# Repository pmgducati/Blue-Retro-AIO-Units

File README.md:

# Blue Retro AIO PCBs
This is a collection of PCBs that I made to work with darthcloud's BlueRetro Project. (https://github.com/darthcloud/BlueRetro)  The PCB's were created in Eagle and I have included the Gerbers if you would like to build them yourself. 

I have created PCB's for all supported systems with the exception of JVS.  An issue has been created for each of the systems that need testing.  If you make one please comment in the related issue on any progress/issues.

Currently, I am working on the Virtual Boy PCB, but need to find a cost efficient controller plug (I am not consolizing mine).  

Amaiorano wrote up a review for the variants that they built, you can read it here:
https://amaiorano.io/2023/11/06/blueretro-aio.html

Current status of all systems:

Here are some pics of the PCBs and Housings:

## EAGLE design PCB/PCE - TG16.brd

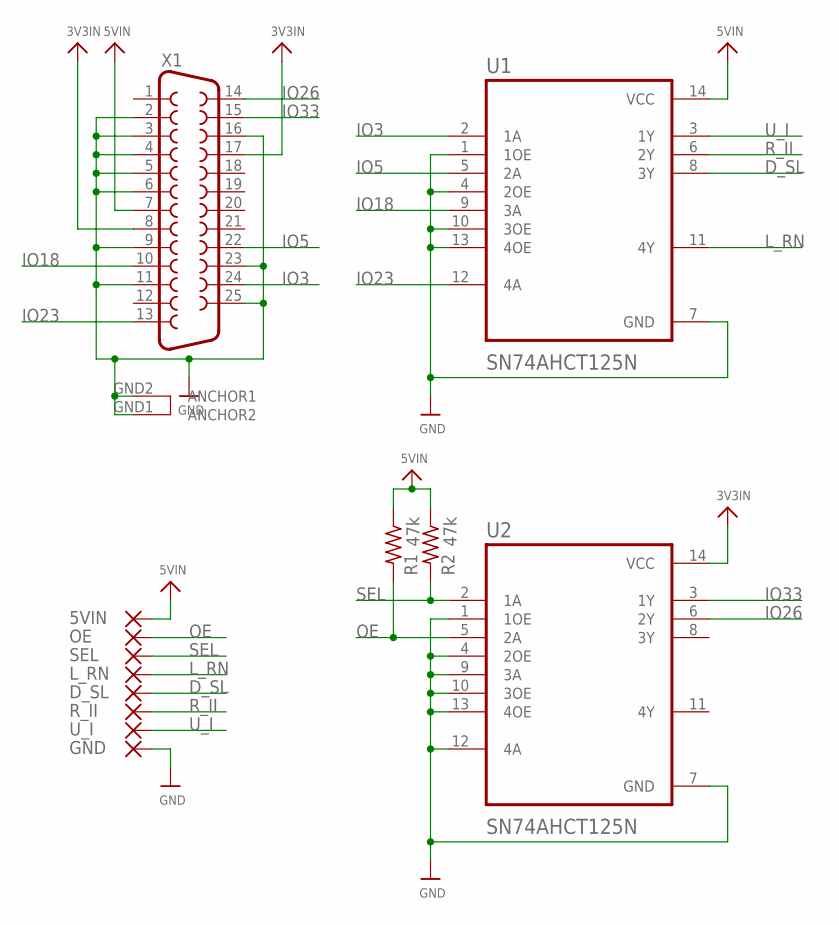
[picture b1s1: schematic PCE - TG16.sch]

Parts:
5VIN: SMD5; SMD2,54-5,08
D_SL: SMD5; SMD2,54-5,08
GND: SMD5; SMD2,54-5,08
L_RN: SMD5; SMD2,54-5,08
OE: SMD5; SMD2,54-5,08
R1, R2: 47k; R1206
R_II: SMD5; SMD2,54-5,08
SEL: SMD5; SMD2,54-5,08
U1, U2: SN74AHCT125N; DIP794W45P254L1969H508Q14
U_I: SMD5; SMD2,54-5,08
X1: DB25_FEMALEHP; F25HP

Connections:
3V3IN: U2.14 (VCC), X1.8, X1.17
5VIN: 5VIN.1, R1.1, R2.1, U1.14 (VCC), X1.7
D_SL: D_SL.1, U1.8 (3Y)
GND: GND.1, U1.1 (1OE), U1.4 (2OE), U1.7 (GND), U1.10 (3OE), U1.13 (4OE), U2.1 (1OE), U2.4 (2OE), U2.7 (GND), U2.9 (3A), U2.10 (3OE), U2.12 (4A), U2.13 (4OE), X1.2, X1.3, X1.4, X1.5, X1.6, X1.9, X1.11, X1.16, X1.23, X1.25, X1.GND1 (ANCHOR2), X1.GND2 (ANCHOR1)
IO3: U1.2 (1A), X1.24
IO5: U1.5 (2A), X1.22
IO18: U1.9 (3A), X1.10
IO23: U1.12 (4A), X1.13
IO26: U2.6 (2Y), X1.14
IO33: U2.3 (1Y), X1.15
L_RN: L_RN.1, U1.11 (4Y)
OE: OE.1, R1.2, U2.5 (2A)
R_II: R_II.1, U1.6 (2Y)
SEL: R2.2, SEL.1, U2.2 (1A)
U_I: U1.3 (1Y), U_I.1

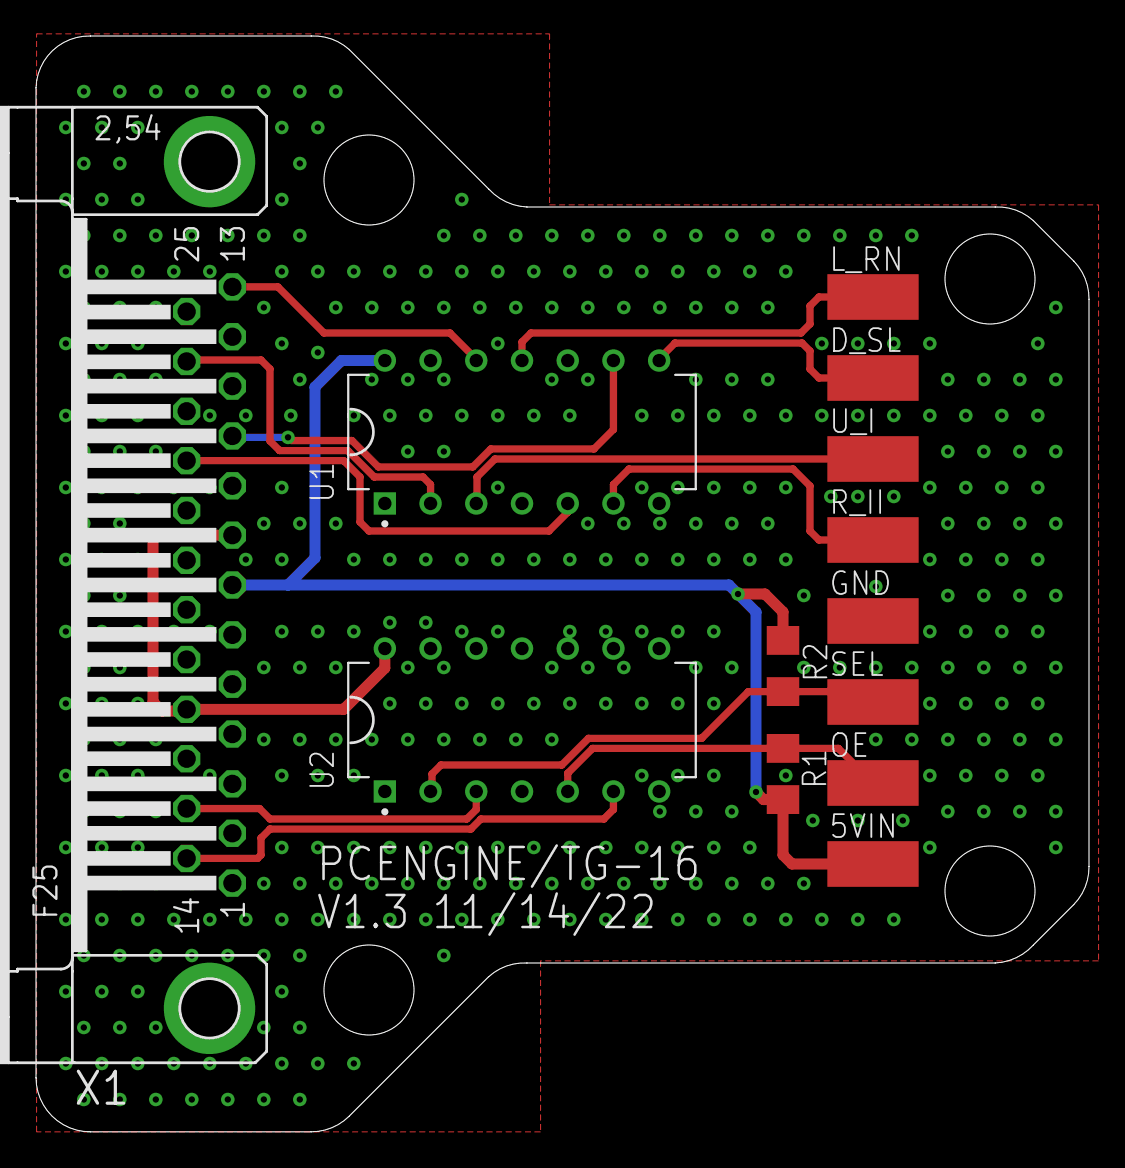
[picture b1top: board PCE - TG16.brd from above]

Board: 2 copper layers, 58.5 x 60.9 mm, 13 parts (0 on the bottom side), 15 nets.

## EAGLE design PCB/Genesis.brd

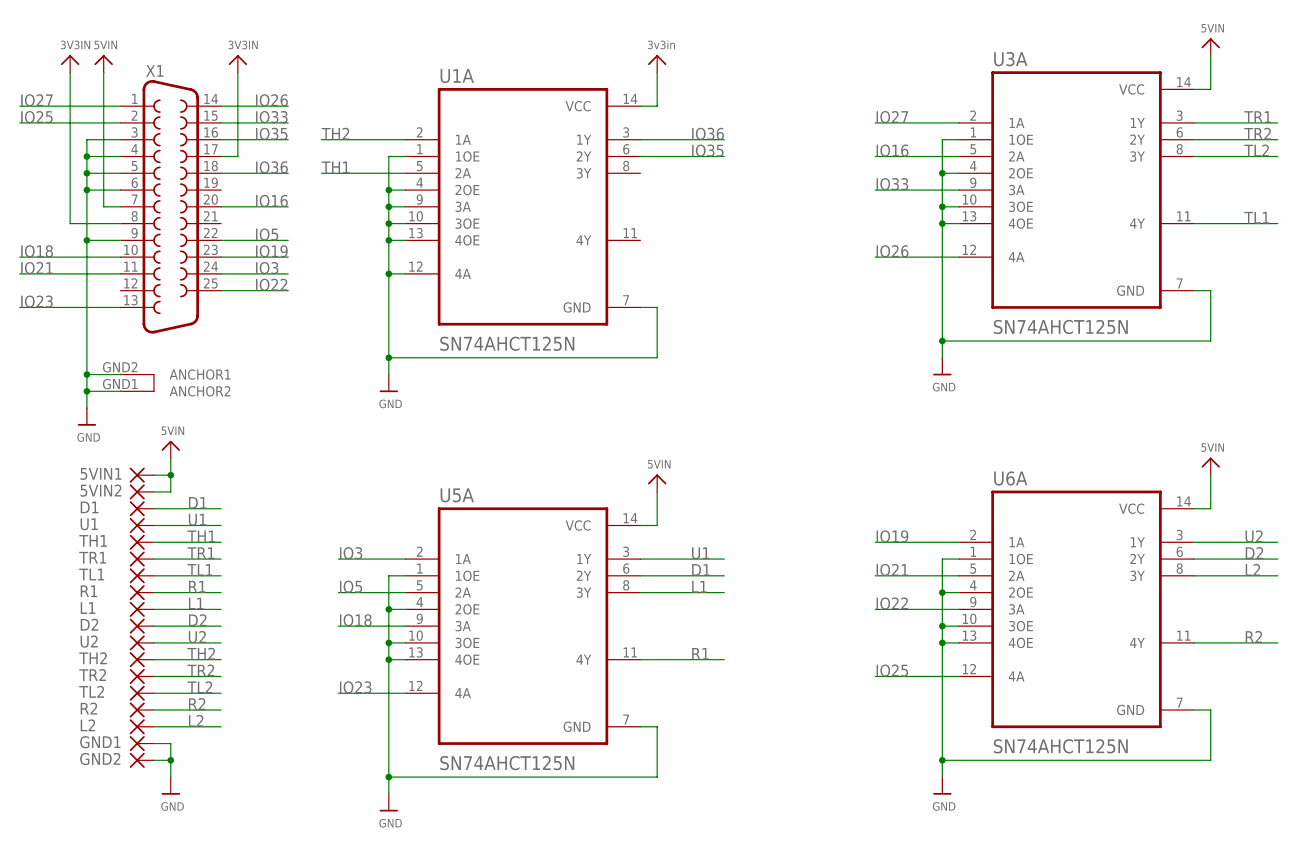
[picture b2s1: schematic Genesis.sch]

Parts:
5VIN1, 5VIN2: SMD5; SMD2,54-5,08
D1, D2: SMD5; SMD2,54-5,08
GND1, GND2: SMD5; SMD2,54-5,08
L1, L2: SMD5; SMD2,54-5,08
R1, R2: SMD5; SMD2,54-5,08
TH1, TH2: SMD5; SMD2,54-5,08
TL1, TL2: SMD5; SMD2,54-5,08
TR1, TR2: SMD5; SMD2,54-5,08
U1, U2: SMD5; SMD2,54-5,08
U1A, U3A, U5A, U6A: SN74AHCT125N; DIP794W45P254L1969H508Q14
X1: DB25_FEMALEHP; F25HP

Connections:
3V3IN: U1A.14 (VCC), X1.8, X1.17
5VIN: 5VIN1.1, 5VIN2.1, U3A.14 (VCC), U5A.14 (VCC), U6A.14 (VCC), X1.7
D1: D1.1, U5A.6 (2Y)
D2: D2.1, U6A.6 (2Y)
GND: GND1.1, GND2.1, U1A.1 (1OE), U1A.4 (2OE), U1A.7 (GND), U1A.9 (3A), U1A.10 (3OE), U1A.12 (4A), U1A.13 (4OE), U3A.1 (1OE), U3A.4 (2OE), U3A.7 (GND), U3A.10 (3OE), U3A.13 (4OE), U5A.1 (1OE), U5A.4 (2OE), U5A.7 (GND), U5A.10 (3OE), U5A.13 (4OE), U6A.1 (1OE), U6A.4 (2OE), U6A.7 (GND), U6A.10 (3OE), U6A.13 (4OE), X1.3, X1.4, X1.5, X1.6, X1.9, X1.GND1 (ANCHOR2), X1.GND2 (ANCHOR1)
IO3: U5A.2 (1A), X1.24
IO5: U5A.5 (2A), X1.22
IO16: U3A.5 (2A), X1.20
IO18: U5A.9 (3A), X1.10
IO19: U6A.2 (1A), X1.23
IO21: U6A.5 (2A), X1.11
IO22: U6A.9 (3A), X1.25
IO23: U5A.12 (4A), X1.13
IO25: U6A.12 (4A), X1.2
IO26: U3A.12 (4A), X1.14
IO27: U3A.2 (1A), X1.1
IO33: U3A.9 (3A), X1.15
IO35: U1A.6 (2Y), X1.16
IO36: U1A.3 (1Y), X1.18
L1: L1.1, U5A.8 (3Y)
L2: L2.1, U6A.8 (3Y)
R1: R1.1, U5A.11 (4Y)
R2: R2.1, U6A.11 (4Y)
TH1: TH1.1, U1A.5 (2A)
TH2: TH2.1, U1A.2 (1A)
TL1: TL1.1, U3A.11 (4Y)
TL2: TL2.1, U3A.8 (3Y)
TR1: TR1.1, U3A.3 (1Y)
TR2: TR2.1, U3A.6 (2Y)
U1: U1.1, U5A.3 (1Y)
U2: U2.1, U6A.3 (1Y)

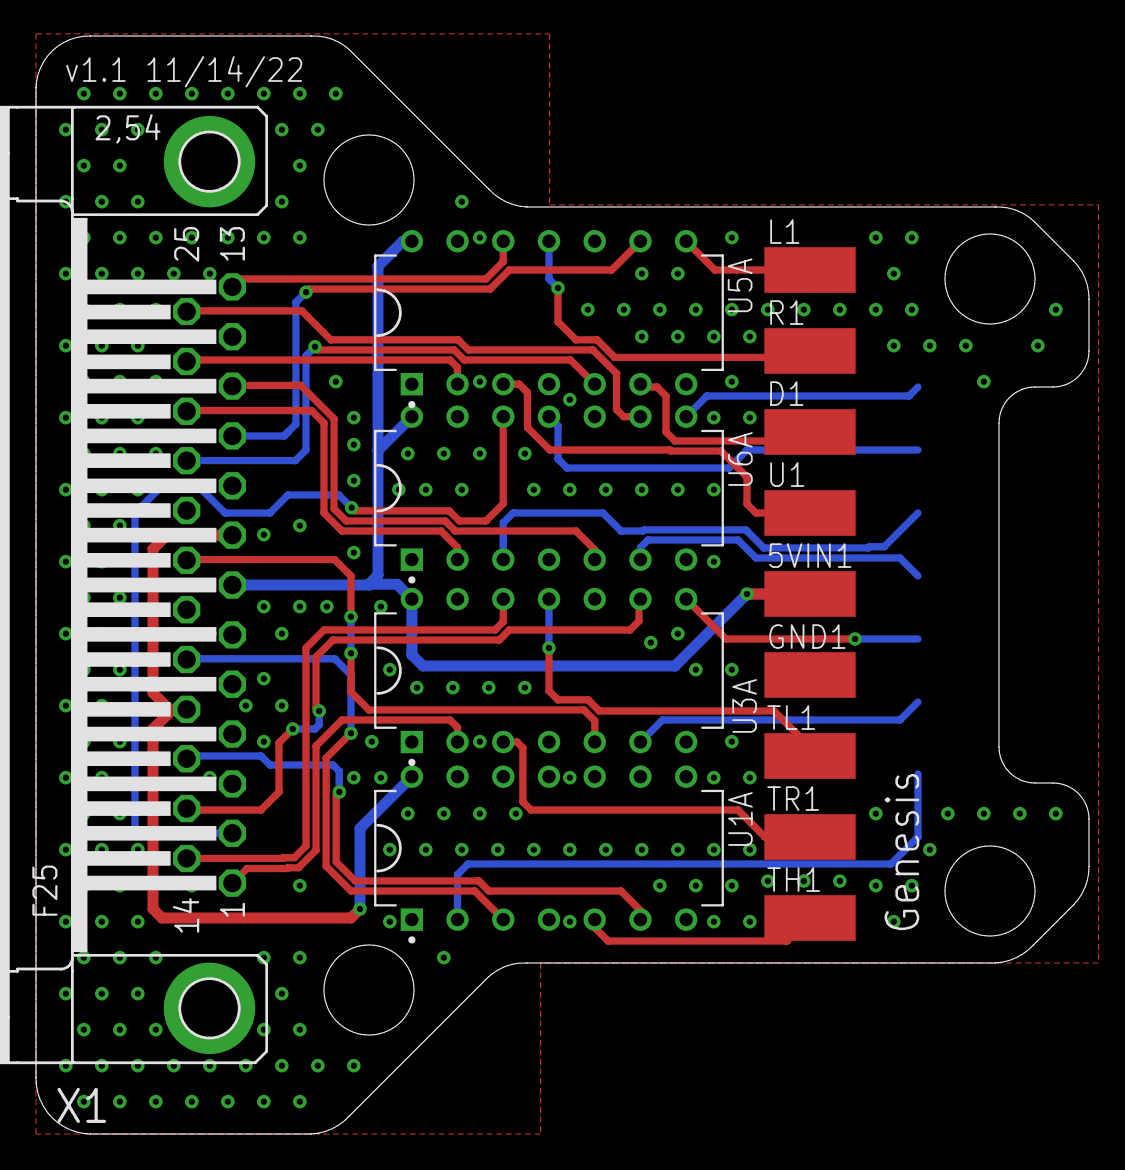
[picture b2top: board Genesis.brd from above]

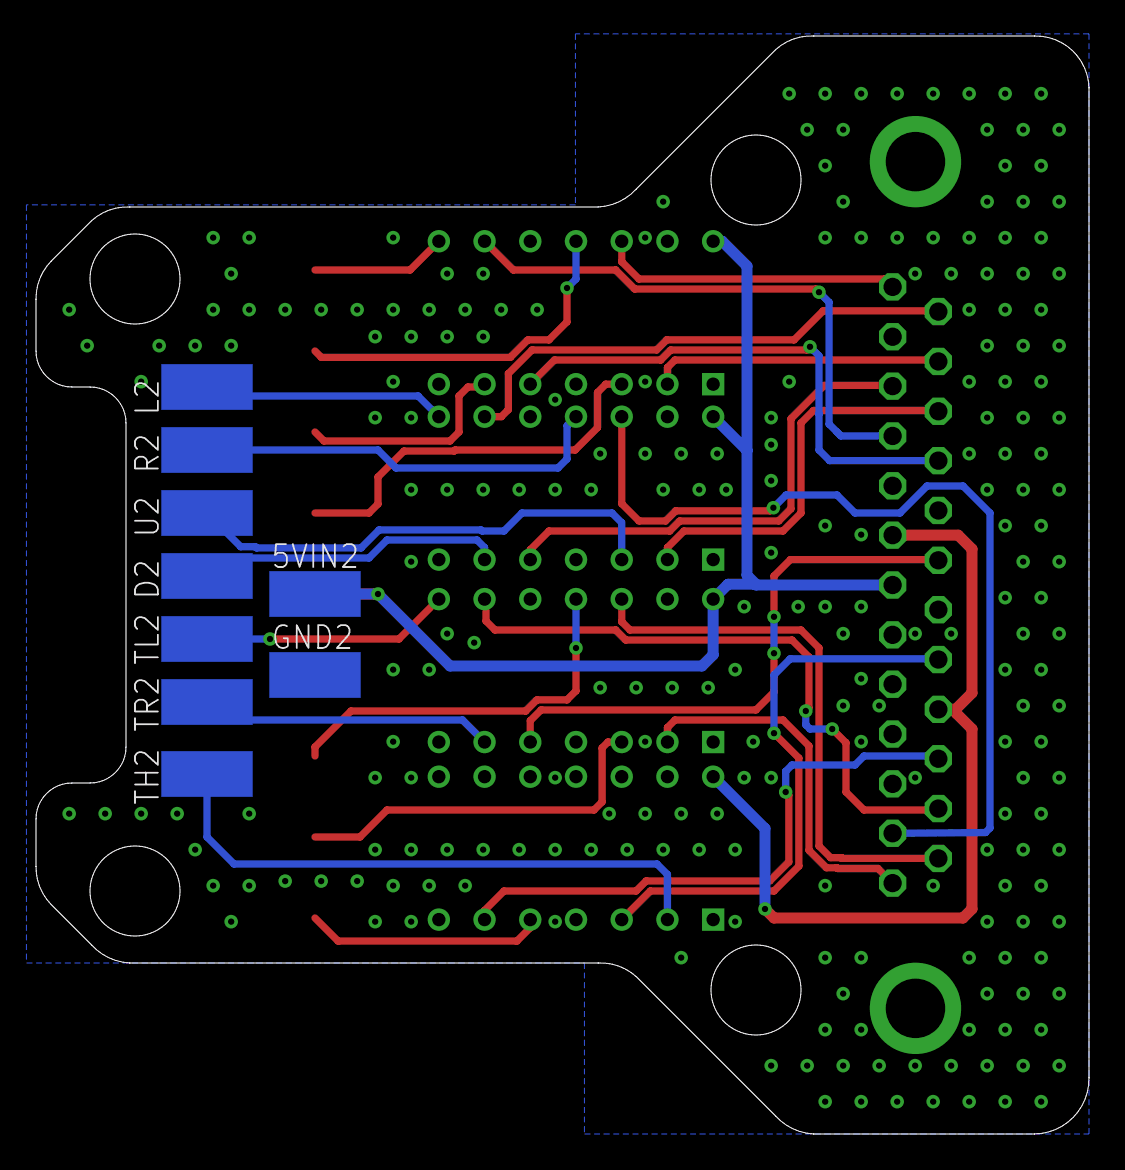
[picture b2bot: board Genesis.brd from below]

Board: 2 copper layers, 58.5 x 61.0 mm, 23 parts (9 on the bottom side), 31 nets.

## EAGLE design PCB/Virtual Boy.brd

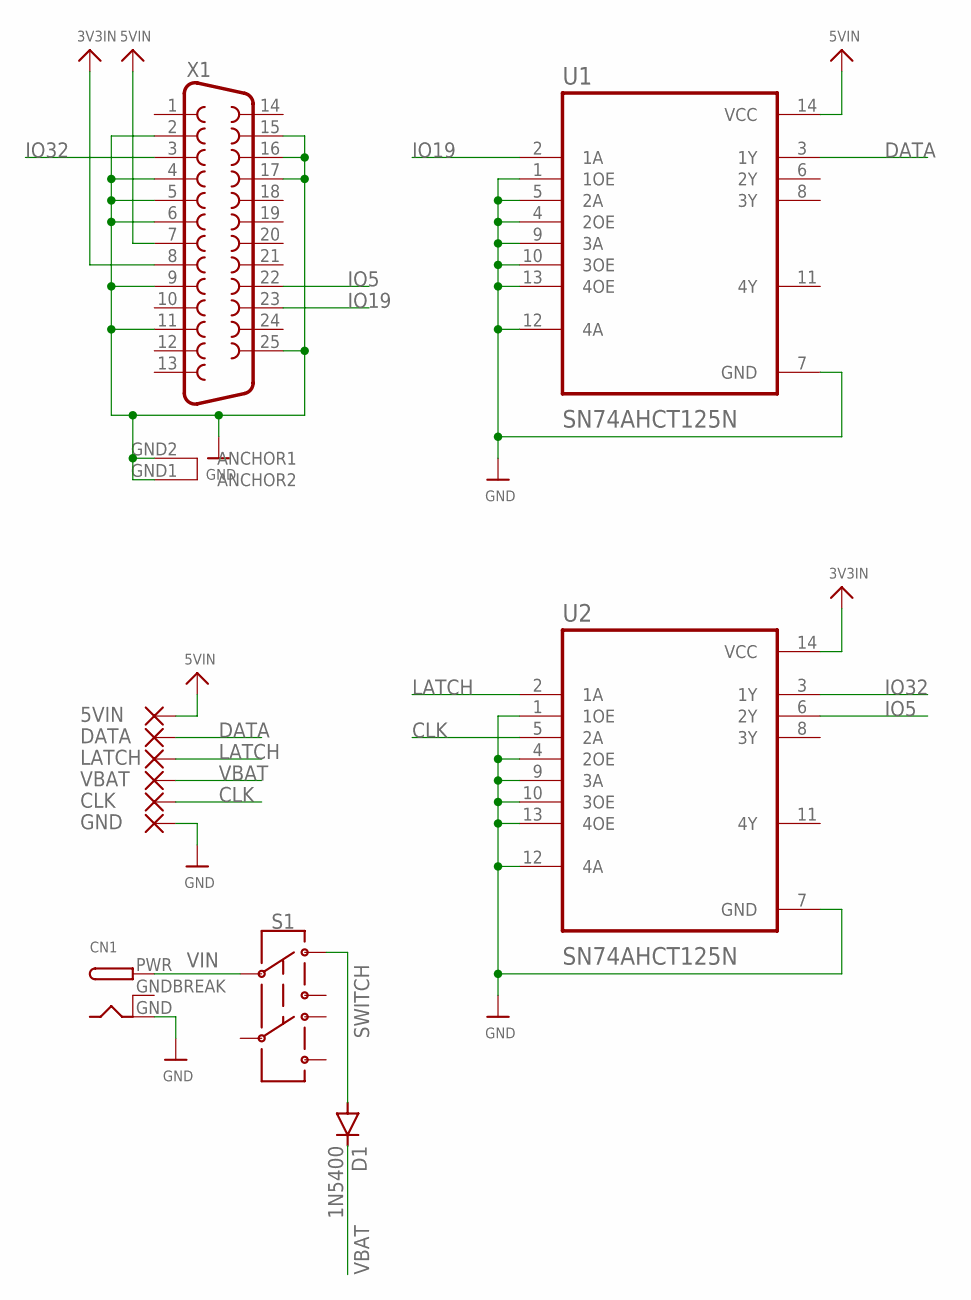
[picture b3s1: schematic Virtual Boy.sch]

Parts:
5VIN: SMD5; SMD2,54-5,08
CLK: SMD5; SMD2,54-5,08
CN1: DCBARRELPTH; DCJACK_2MM_PTH
D1: 1N5400; DO201-15
DATA: SMD5; SMD2,54-5,08
GND: SMD5; SMD2,54-5,08
LATCH: SMD5; SMD2,54-5,08
S1: SWITCH-DPDT-PTH-GPI-152-3013; SWITCH_DPDT_PTH_GPI-152-3013
U1, U2: SN74AHCT125N; DIP794W45P254L1969H508Q14
VBAT: SMD5; SMD2,54-5,08
X1: DB25_FEMALEHP; F25HP

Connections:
3V3IN: U2.14 (VCC), X1.8
5VIN: 5VIN.1, U1.14 (VCC), X1.7
CLK: CLK.1, U2.5 (2A)
DATA: DATA.1, U1.3 (1Y)
GND: CN1.GND, GND.1, U1.1 (1OE), U1.4 (2OE), U1.5 (2A), U1.7 (GND), U1.9 (3A), U1.10 (3OE), U1.12 (4A), U1.13 (4OE), U2.1 (1OE), U2.4 (2OE), U2.7 (GND), U2.9 (3A), U2.10 (3OE), U2.12 (4A), U2.13 (4OE), X1.2, X1.4, X1.5, X1.6, X1.9, X1.11, X1.15, X1.16, X1.17, X1.25, X1.GND1 (ANCHOR2), X1.GND2 (ANCHOR1)
GNDBREAK: CN1.GNDBREAK
IO5: U2.6 (2Y), X1.22
IO19: U1.2 (1A), X1.23
IO32: U2.3 (1Y), X1.3
LATCH: LATCH.1, U2.2 (1A)
SWITCH: D1.A, S1.10 (1)
VBAT: D1.C, VBAT.1
VIN: CN1.PWR, S1.C@1 (2)

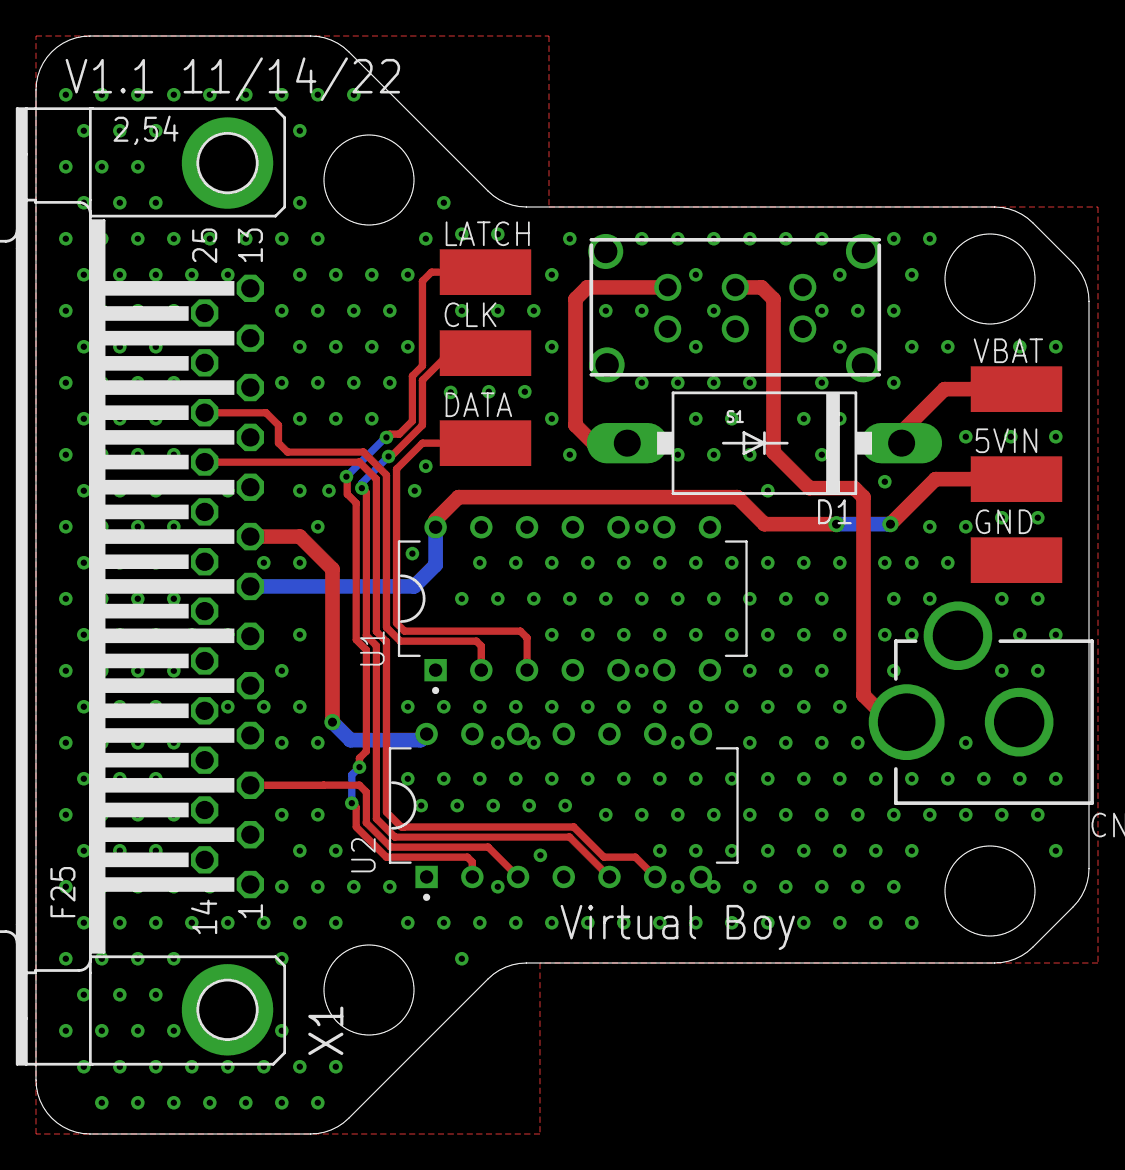
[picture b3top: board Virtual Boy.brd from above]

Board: 2 copper layers, 58.5 x 61.0 mm, 12 parts (0 on the bottom side), 12 nets.

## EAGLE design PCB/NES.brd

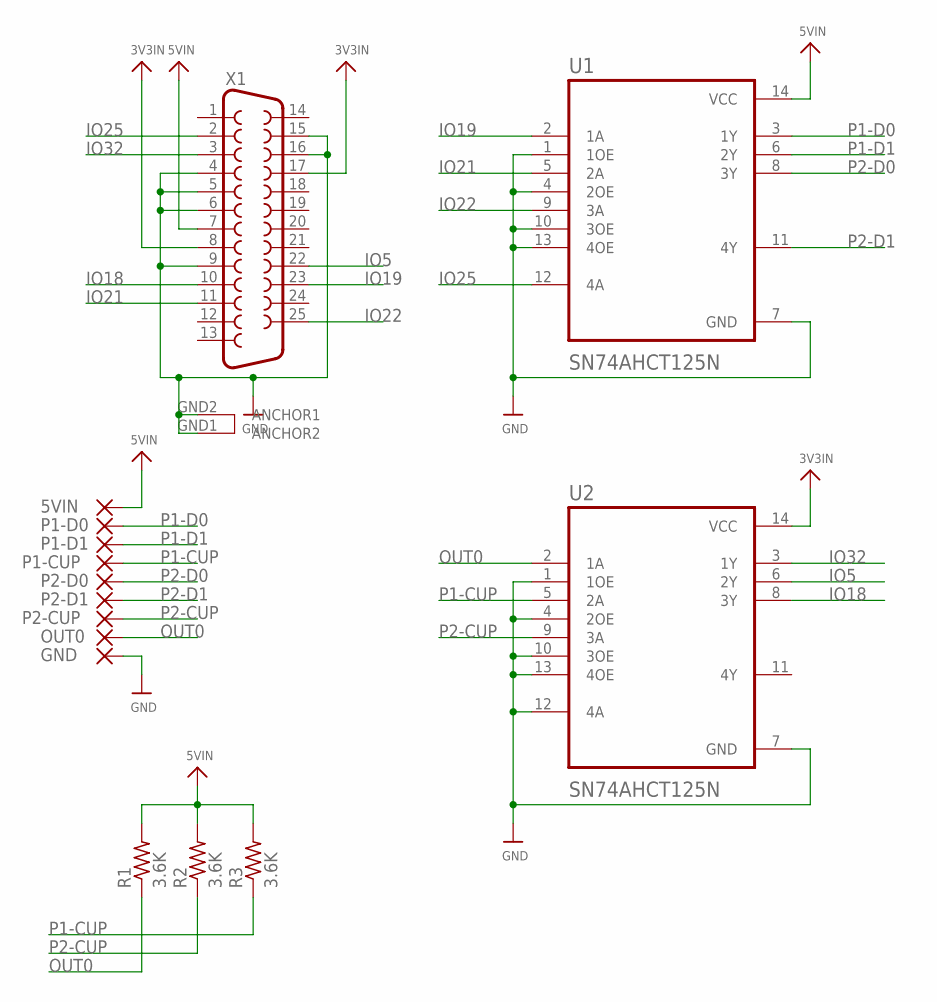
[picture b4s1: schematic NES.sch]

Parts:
5VIN: SMD5; SMD2,54-5,08
GND: SMD5; SMD2,54-5,08
OUT0: SMD5; SMD2,54-5,08
P1-CUP, P1-D0, P1-D1, P2-CUP, P2-D0, P2-D1: SMD5; SMD2,54-5,08
R1, R2, R3: 3.6K; R1206
U1, U2: SN74AHCT125N; DIP794W45P254L1969H508Q14
X1: DB25_FEMALEHP; F25HP

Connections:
3V3IN: U2.14 (VCC), X1.8, X1.17
5VIN: 5VIN.1, R1.2, R2.2, R3.2, U1.14 (VCC), X1.7
GND: GND.1, U1.1 (1OE), U1.4 (2OE), U1.7 (GND), U1.10 (3OE), U1.13 (4OE), U2.1 (1OE), U2.4 (2OE), U2.7 (GND), U2.10 (3OE), U2.12 (4A), U2.13 (4OE), X1.4, X1.5, X1.6, X1.9, X1.15, X1.16, X1.GND1 (ANCHOR2), X1.GND2 (ANCHOR1)
IO5: U2.6 (2Y), X1.22
IO18: U2.8 (3Y), X1.10
IO19: U1.2 (1A), X1.23
IO21: U1.5 (2A), X1.11
IO22: U1.9 (3A), X1.25
IO25: U1.12 (4A), X1.2
IO32: U2.3 (1Y), X1.3
OUT0: OUT0.1, R1.1, U2.2 (1A)
P1-CUP: P1-CUP.1, R3.1, U2.5 (2A)
P1-D0: P1-D0.1, U1.3 (1Y)
P1-D1: P1-D1.1, U1.6 (2Y)
P2-CUP: P2-CUP.1, R2.1, U2.9 (3A)
P2-D0: P2-D0.1, U1.8 (3Y)
P2-D1: P2-D1.1, U1.11 (4Y)

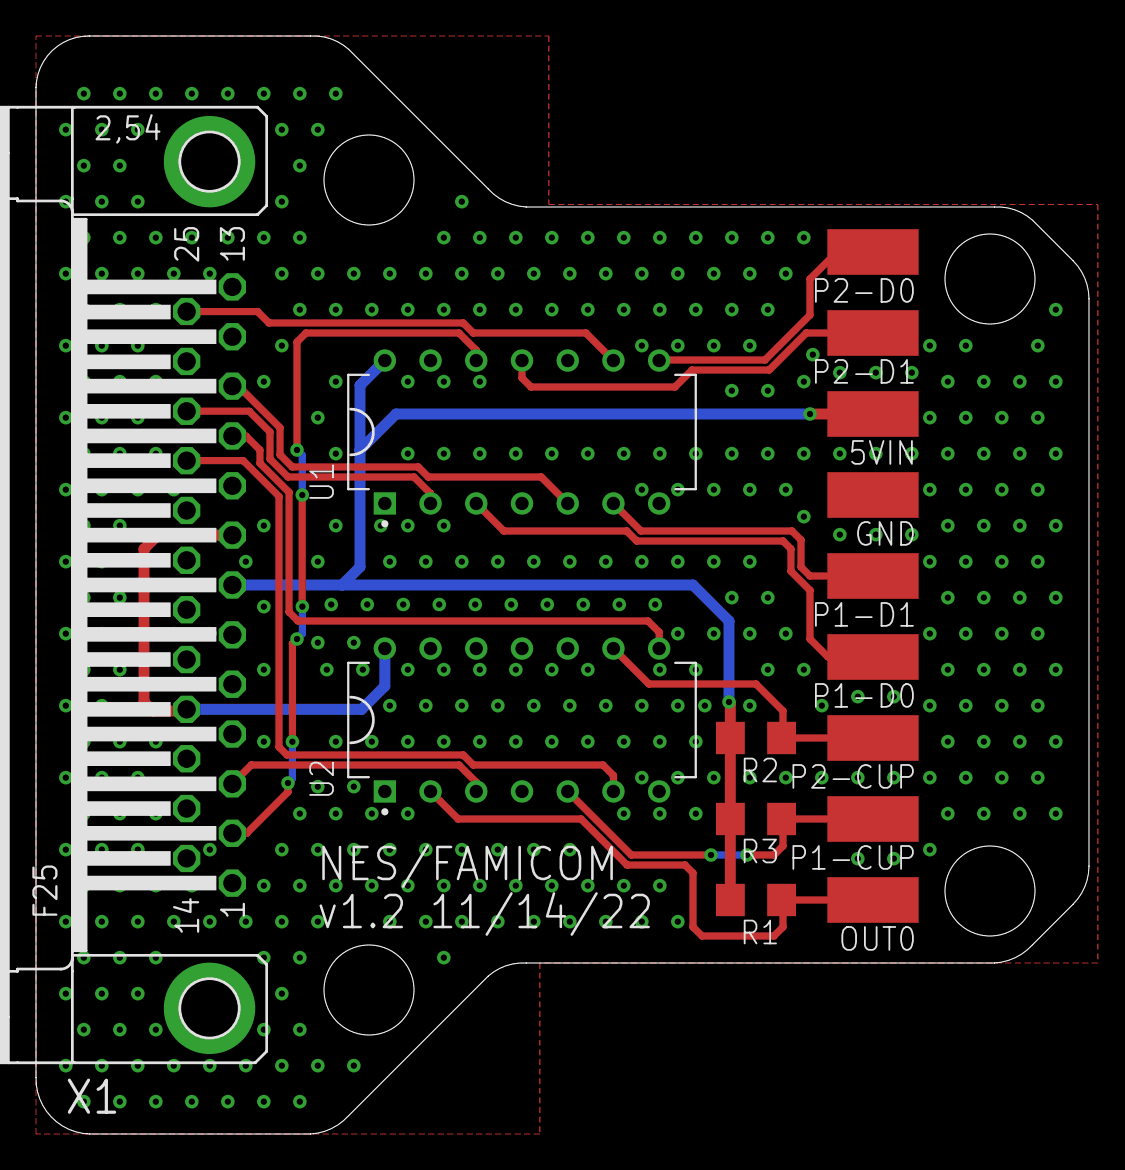
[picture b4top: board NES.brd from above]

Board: 2 copper layers, 58.5 x 61.0 mm, 15 parts (0 on the bottom side), 17 nets.

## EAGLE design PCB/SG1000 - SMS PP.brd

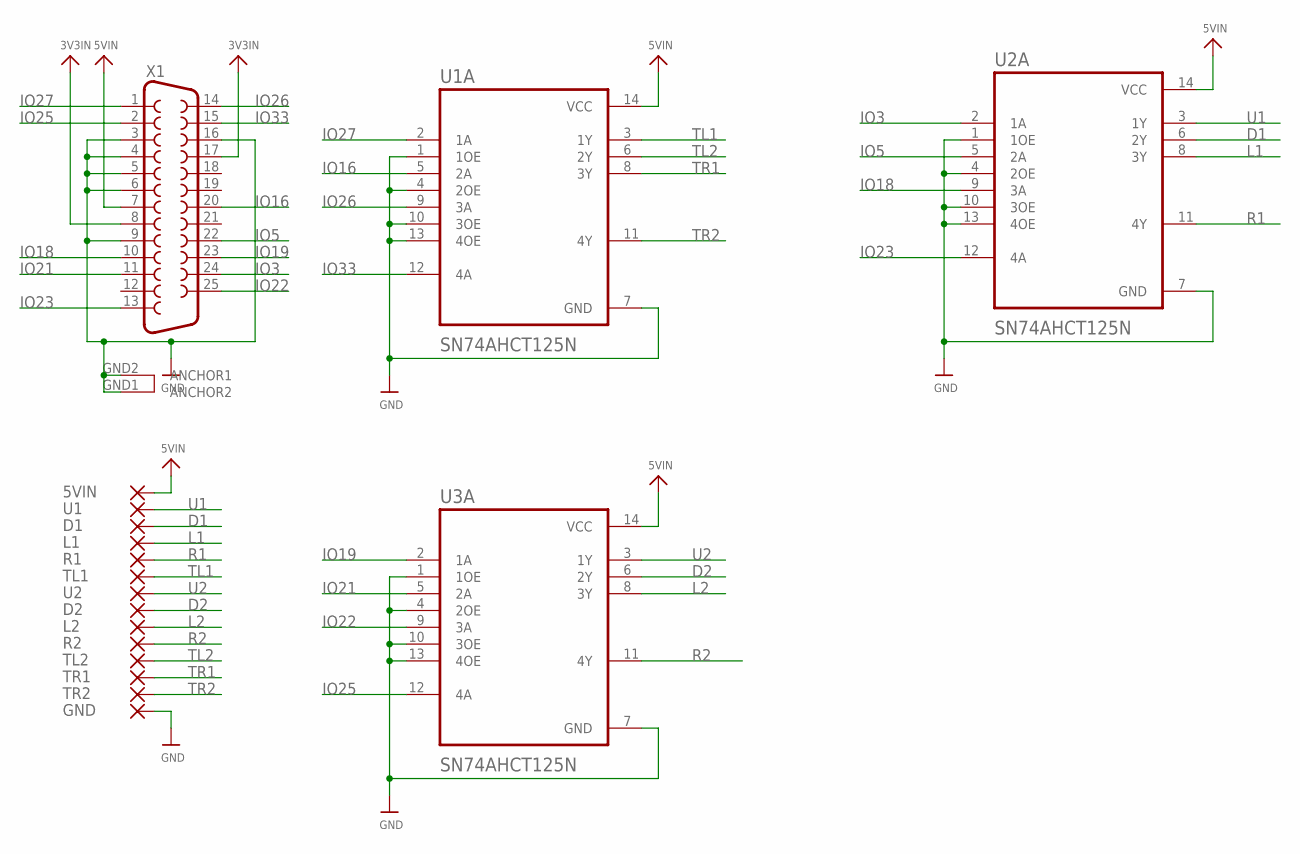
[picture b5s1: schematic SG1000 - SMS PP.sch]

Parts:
5VIN: SMD5; SMD2,54-5,08
D1, D2: SMD5; SMD2,54-5,08
GND: SMD5; SMD2,54-5,08
L1, L2: SMD5; SMD2,54-5,08
R1, R2: SMD5; SMD2,54-5,08
TL1, TL2: SMD5; SMD2,54-5,08
TR1, TR2: SMD5; SMD2,54-5,08
U1, U2: SMD5; SMD2,54-5,08
U1A, U2A, U3A: SN74AHCT125N; DIP794W45P254L1969H508Q14
X1: DB25_FEMALEHP; F25HP

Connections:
3V3IN: X1.8, X1.17
5VIN: 5VIN.1, U1A.14 (VCC), U2A.14 (VCC), U3A.14 (VCC), X1.7
D1: D1.1, U2A.6 (2Y)
D2: D2.1, U3A.6 (2Y)
GND: GND.1, U1A.1 (1OE), U1A.4 (2OE), U1A.7 (GND), U1A.10 (3OE), U1A.13 (4OE), U2A.1 (1OE), U2A.4 (2OE), U2A.7 (GND), U2A.10 (3OE), U2A.13 (4OE), U3A.1 (1OE), U3A.4 (2OE), U3A.7 (GND), U3A.10 (3OE), U3A.13 (4OE), X1.3, X1.4, X1.5, X1.6, X1.9, X1.16, X1.GND1 (ANCHOR2), X1.GND2 (ANCHOR1)
IO3: U2A.2 (1A), X1.24
IO5: U2A.5 (2A), X1.22
IO16: U1A.5 (2A), X1.20
IO18: U2A.9 (3A), X1.10
IO19: U3A.2 (1A), X1.23
IO21: U3A.5 (2A), X1.11
IO22: U3A.9 (3A), X1.25
IO23: U2A.12 (4A), X1.13
IO25: U3A.12 (4A), X1.2
IO26: U1A.9 (3A), X1.14
IO27: U1A.2 (1A), X1.1
IO33: U1A.12 (4A), X1.15
L1: L1.1, U2A.8 (3Y)
L2: L2.1, U3A.8 (3Y)
R1: R1.1, U2A.11 (4Y)
R2: R2.1, U3A.11 (4Y)
TL1: TL1.1, U1A.3 (1Y)
TL2: TL2.1, U1A.6 (2Y)
TR1: TR1.1, U1A.8 (3Y)
TR2: TR2.1, U1A.11 (4Y)
U1: U1.1, U2A.3 (1Y)
U2: U2.1, U3A.3 (1Y)

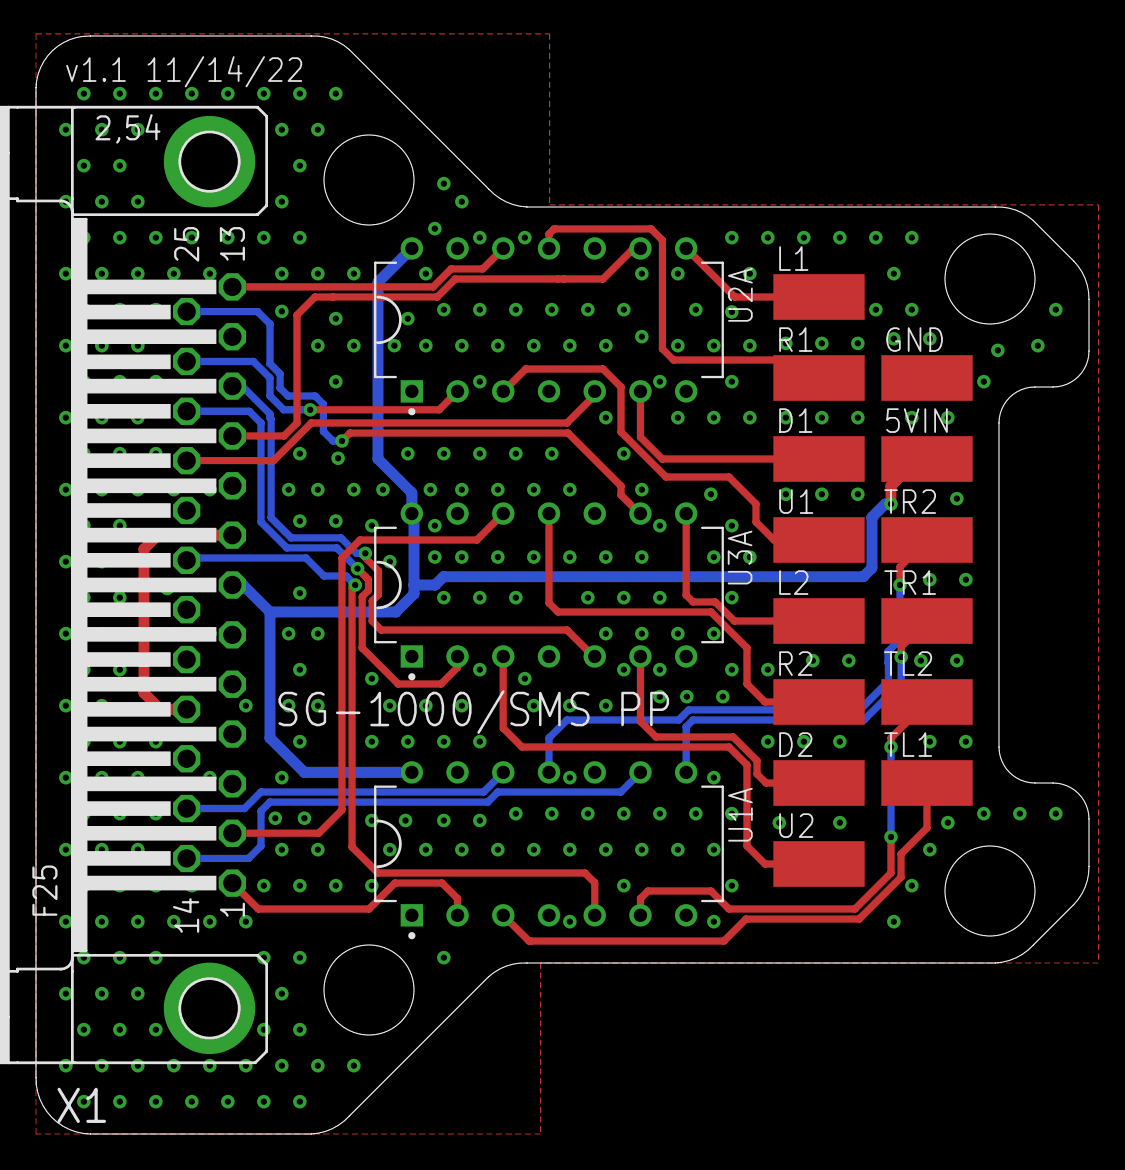
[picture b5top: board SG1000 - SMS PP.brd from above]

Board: 2 copper layers, 58.5 x 61.0 mm, 18 parts (0 on the bottom side), 27 nets.

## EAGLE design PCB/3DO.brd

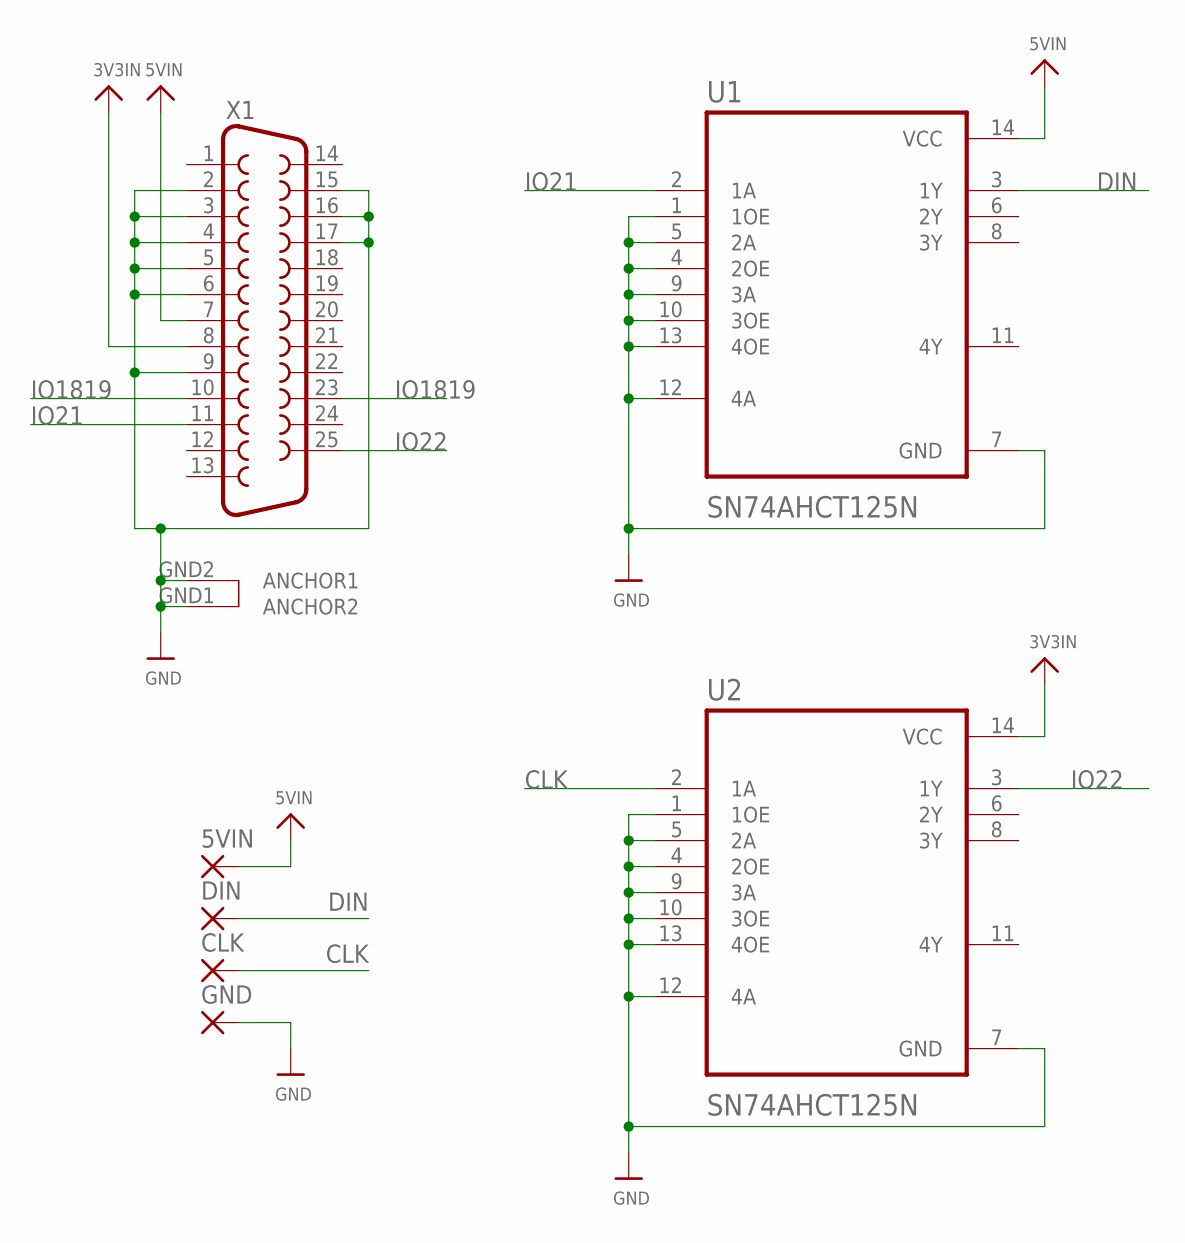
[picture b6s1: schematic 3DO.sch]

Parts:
5VIN: SMD5; SMD2,54-5,08
CLK: SMD5; SMD2,54-5,08
DIN: SMD5; SMD2,54-5,08
GND: SMD5; SMD2,54-5,08
U1, U2: SN74AHCT125N; DIP794W45P254L1969H508Q14
X1: DB25_FEMALEHP; F25HP

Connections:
3V3IN: U2.14 (VCC), X1.8
5VIN: 5VIN.1, U1.14 (VCC), X1.7
CLK: CLK.1, U2.2 (1A)
DIN: DIN.1, U1.3 (1Y)
GND: GND.1, U1.1 (1OE), U1.4 (2OE), U1.5 (2A), U1.7 (GND), U1.9 (3A), U1.10 (3OE), U1.12 (4A), U1.13 (4OE), U2.1 (1OE), U2.4 (2OE), U2.5 (2A), U2.7 (GND), U2.9 (3A), U2.10 (3OE), U2.12 (4A), U2.13 (4OE), X1.2, X1.3, X1.4, X1.5, X1.6, X1.9, X1.15, X1.16, X1.17, X1.GND1 (ANCHOR2), X1.GND2 (ANCHOR1)
IO21: U1.2 (1A), X1.11
IO22: U2.3 (1Y), X1.25
IO1819: X1.10, X1.23

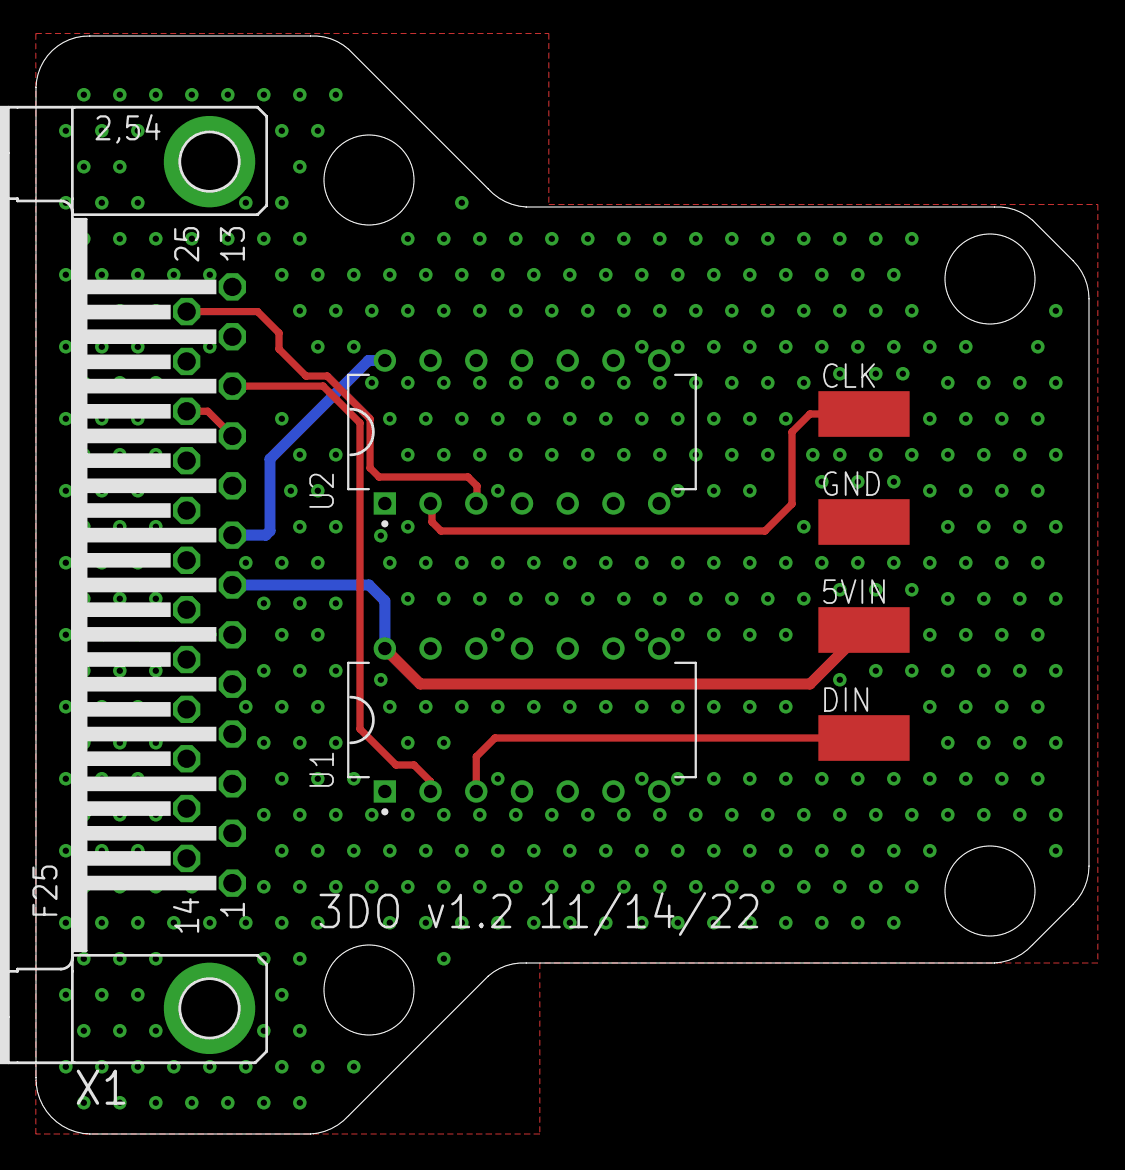
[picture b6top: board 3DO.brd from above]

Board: 2 copper layers, 58.5 x 61.0 mm, 7 parts (0 on the bottom side), 8 nets.

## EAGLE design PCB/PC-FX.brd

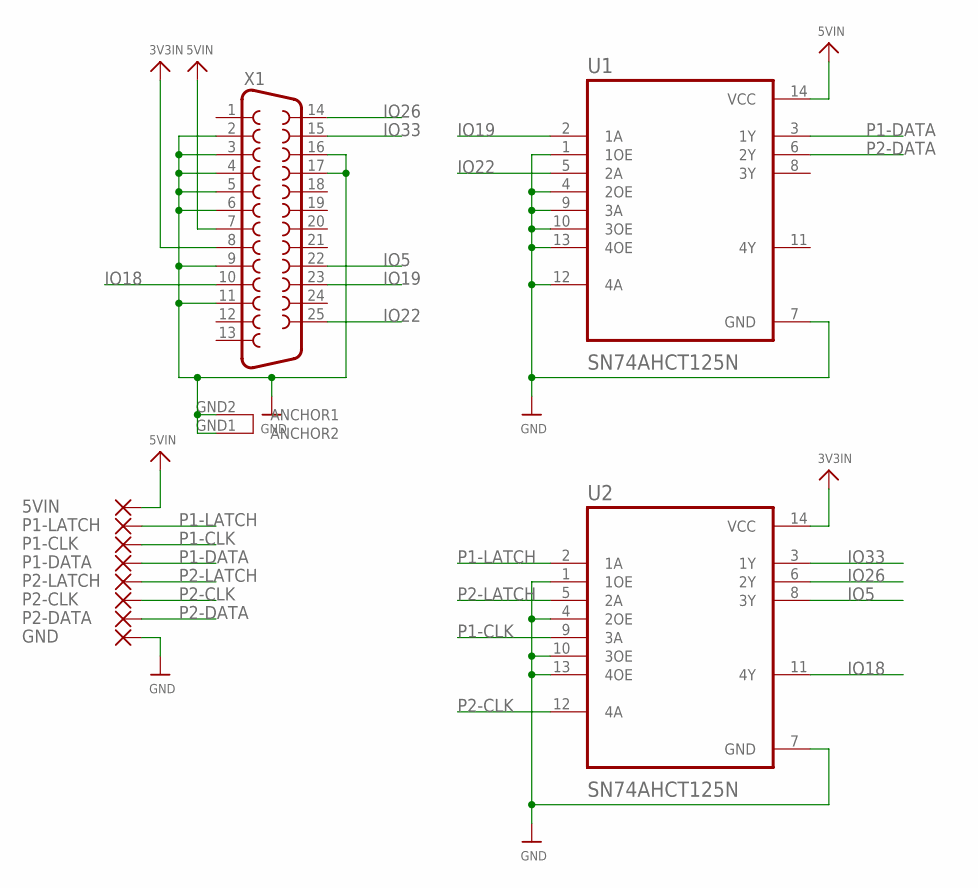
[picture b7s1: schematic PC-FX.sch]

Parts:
5VIN: SMD5; SMD2,54-5,08
GND: SMD5; SMD2,54-5,08
P1-CLK, P1-DATA, P1-LATCH, P2-CLK, P2-DATA, P2-LATCH: SMD5; SMD2,54-5,08
U1, U2: SN74AHCT125N; DIP794W45P254L1969H508Q14
X1: DB25_FEMALEHP; F25HP

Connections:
3V3IN: U2.14 (VCC), X1.8
5VIN: 5VIN.1, U1.14 (VCC), X1.7
GND: GND.1, U1.1 (1OE), U1.4 (2OE), U1.7 (GND), U1.9 (3A), U1.10 (3OE), U1.12 (4A), U1.13 (4OE), U2.1 (1OE), U2.4 (2OE), U2.7 (GND), U2.10 (3OE), U2.13 (4OE), X1.2, X1.3, X1.4, X1.5, X1.6, X1.9, X1.11, X1.16, X1.17, X1.GND1 (ANCHOR2), X1.GND2 (ANCHOR1)
IO5: U2.8 (3Y), X1.22
IO18: U2.11 (4Y), X1.10
IO19: U1.2 (1A), X1.23
IO22: U1.5 (2A), X1.25
IO26: U2.6 (2Y), X1.14
IO33: U2.3 (1Y), X1.15
P1-CLK: P1-CLK.1, U2.9 (3A)
P1-DATA: P1-DATA.1, U1.3 (1Y)
P1-LATCH: P1-LATCH.1, U2.2 (1A)
P2-CLK: P2-CLK.1, U2.12 (4A)
P2-DATA: P2-DATA.1, U1.6 (2Y)
P2-LATCH: P2-LATCH.1, U2.5 (2A)

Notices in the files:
parts and their libraries:
SparkFun-Retired: Licensing: Creative Commons ShareAlike 4.0 International - https://creativecommons.org/licenses/by-sa/4.0
microbuilder: This work is placed in the public domain, and may be freely used for commercial and non-commercial work with the following conditions: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
